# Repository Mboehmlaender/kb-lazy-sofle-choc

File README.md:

<div align="center">
  
<!-- Badges -->
<p>

</p>
   
<h4>
    <a href="https://github.com/Mboehmlaender/kb-lazy-sofle-choc">Documentation</a>
  <span> · </span>
    <a href="https://github.com/Mboehmlaender/kb-lazy-sofle-choc/issues/">Report Bug</a>
  <span> · </span>
    <a href="https://github.com/Mboehmlaender/kb-lazy-sofle-choc/issues/">Request Feature</a>
  </h4>
</div>

<br />
  <!--  -->
  <h1>LazySofleChoc</h1>
  
  <p>
The origianal Sofle is a 6×4+5 keys column-staggered split keyboard with encoder support. Based on [Lily58](https://github.com/kata0510/Lily58), [Corne](https://github.com/foostan/crkbd) and [Helix](https://github.com/MakotoKurauchi/helix) keyboards.

I removed three of the five thumb-cluster keys as i do not need them and i switched the firmware to VIAL. Those are the only varations that were made.

**[For more information and documentation visit https://josefadamcik.github.io/SofleKeyboard/](https://josefadamcik.github.io/SofleKeyboard/)**

SofleKeyboard was created by [Josef Adamcik](https://josef-adamcik.cz/). The motivation and process is covered in following blog-post: [Let me introduce you SofleKeyboard - a split keyboard based on Lily58 and Crkbd](https://josef-adamcik.cz/electronics/let-me-introduce-you-sofle-keyboard-split-keyboard-based-on-lily58.html). The Sofle Choc was designed by Brian Low and based on the excellent Sofle RGB by Dane Evans which was based on the original Sofle v2 by Josef Adamčík.

Sofle RGB was contributed by [Dane Evans](https://github.com/DaneEvans).

Sofle soldered was contributed by [kb-elmo](https://github.com/kb-elmo)

</p>

<!-- Table of Contents -->
# Table of Contents

- [About the Project](#about-the-project)
- [Features](#features)
- [Getting Started](#getting-started)
  * [List of materials](#list-of-materials)
  * [Necessary tools](#necessary-tools) 
  * [Optional tools](#optional-tools)
- [Build Guide](#build-guide)
- [Firmware](#firmware)
- [FAQ](#faq)
- [License](#license)
- [Acknowledgements](#acknowledgements)

<!-- About the Project -->
## About the Project
Description

<div align="center"> 
  
</div>

<!-- Features -->
### Features

- Feature 1
- Feature 2
- Feature 3

<!-- Getting Started -->
## Getting Started

<!-- List of Materials -->
### List of Materials

- 
- 
- 

<!-- Necessary tools -->
### Necessary tools
- 
-
-
   
<!-- Optional tools -->
### Optional tools
- 
-
-

<!-- Build Guide -->
### Build Guide

There is a detailled guide on how to build the Sofle Choc by Brian Lowe. Please refer to [this site](https://brianlow.notion.site/Sofle-Choc-Build-Guide-c4bbbaece6e746f7a5956842af567e79).

<!-- Firmware -->
## Firmware 

Sofle uses [Vial firmware](https://github.com/vial-kb/vial-qmk)

<!-- FAQ -->
## FAQ

- Question 1

  + Answer 1

- Question 2

  + Answer 2

<!-- License -->
## License

Licensed under MIT license

LazySofleChoc Project contains changes to the original product and / or the original product.
Sofle Choc under the MIT license.

Copyright (c) 2018 Josef Adamcik
https://github.com/josefadamcik/SofleKeyboard

SofleKeyboard Project contains changes to the original product and / or the original product.
Lily58 under the MIT license.

Copyright (c) 2018 Naoki Katahira
https://github.com/kata0510/Lily58

Lily58 Project contains changes to the original product and / or the original product.
Helix under the MIT license.

Copyright (c) 2018 MakotoKurauchi
https://github.com/MakotoKurauchi/helix

Lily58 Project contains changes to the original product and / or the original product.
crkbd under the MIT license.

Copyright (c) 2018 foostan
https://github.com/foostan/crkbd

Lily58 Project contains changes to the original product and / or the original product.
Ergo42 under the MIT license.

Copyright (c) 2017 Biacco42
https://github.com/Biacco42/Ergo42

<!-- Acknowledgments -->
## Acknowledgements

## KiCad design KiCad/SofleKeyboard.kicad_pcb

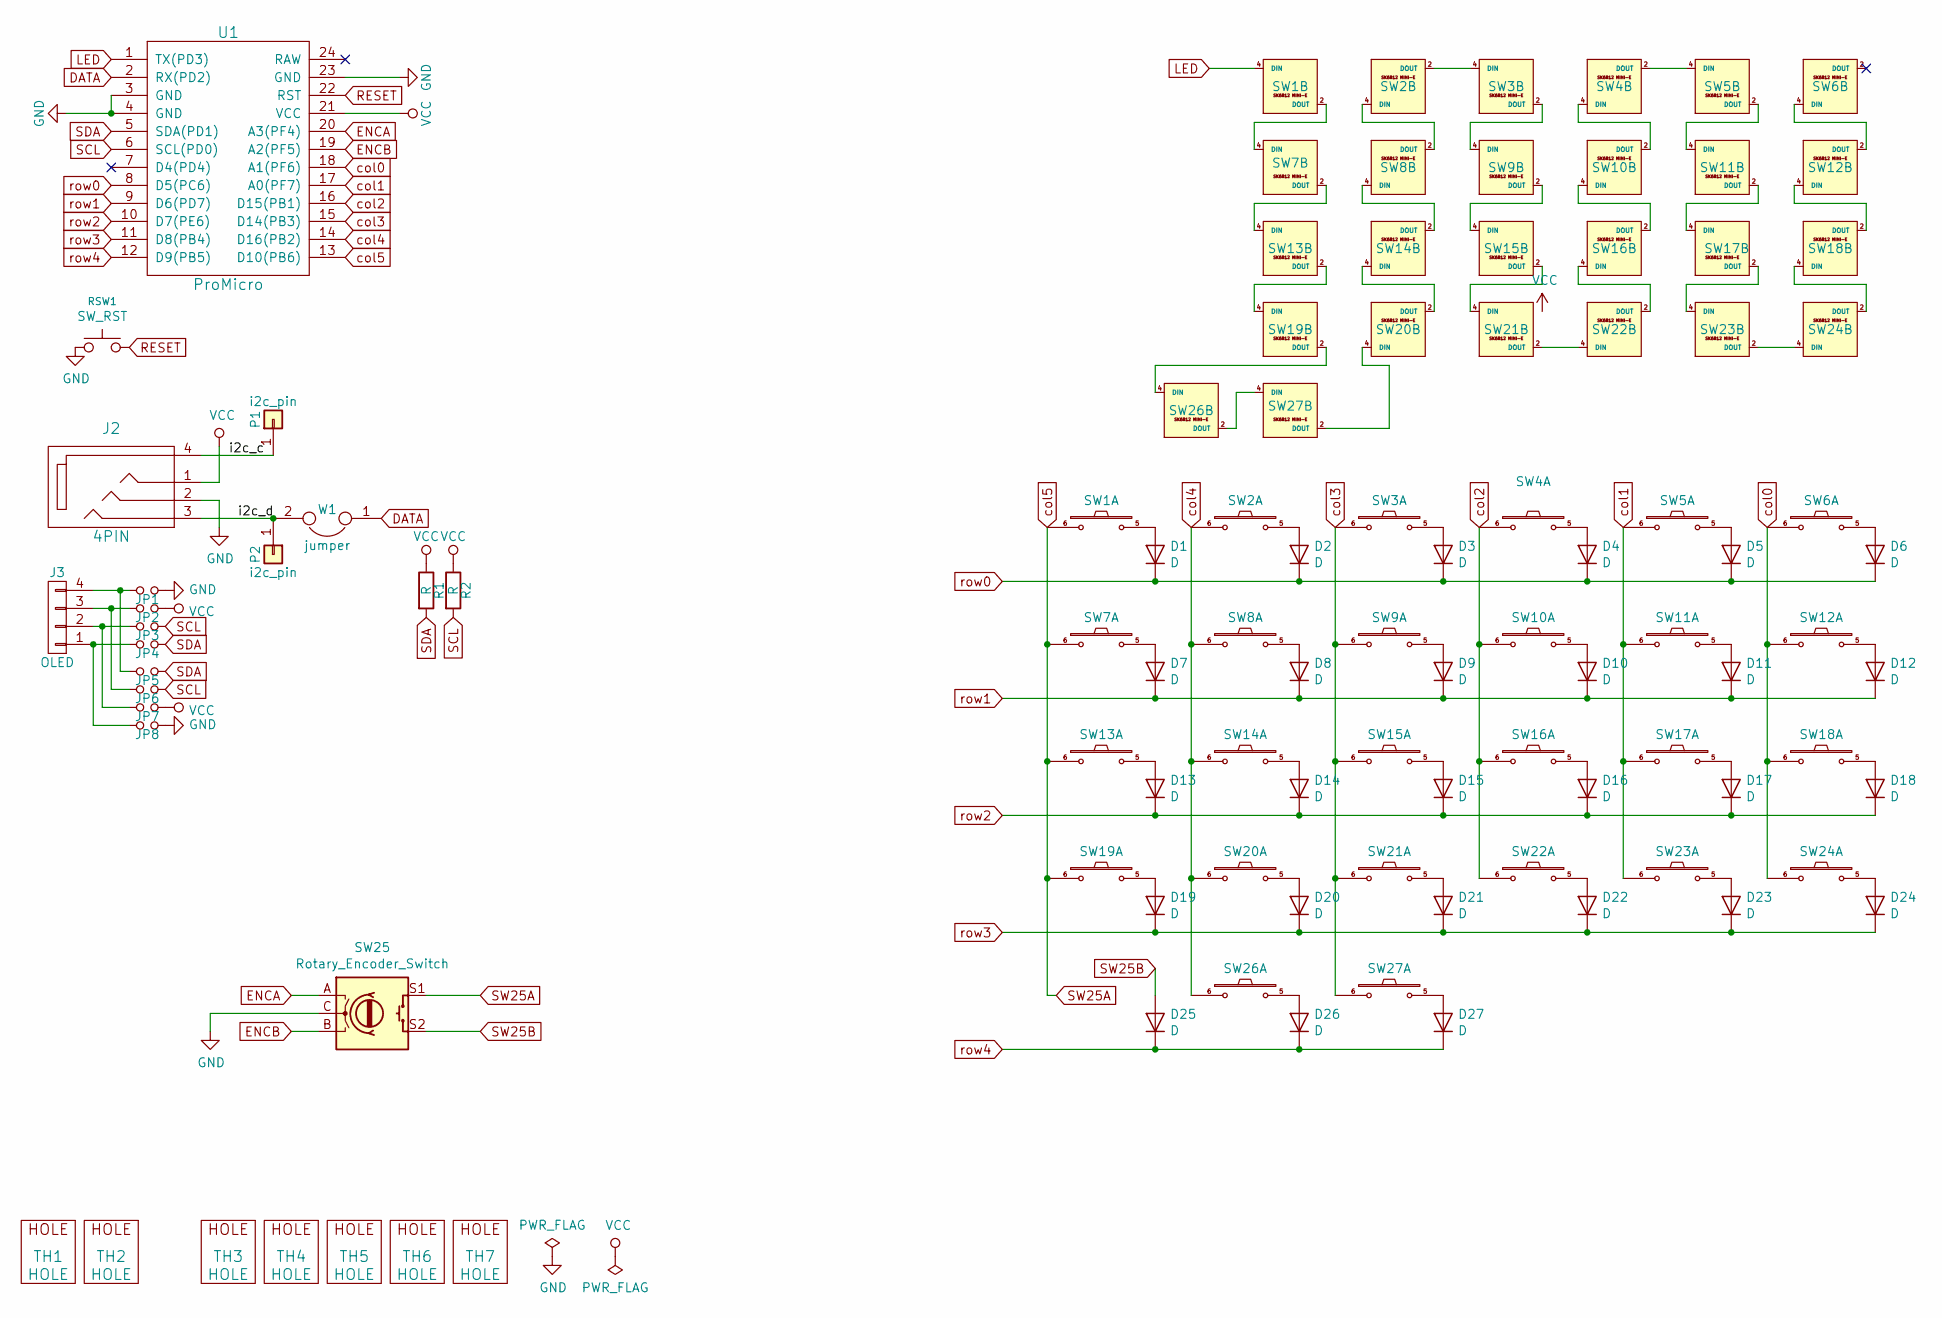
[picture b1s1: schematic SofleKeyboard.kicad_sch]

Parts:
D1, D2, D3, D4, D5, D6, D7, D8, D9, D10, D11, D12, D13, D14, D15, D16, D17, D18, D19, D20, D21, D22, D23, D24, D25, D26, D27: D; crkbd-diode
J2: 4PIN; MJ-4PP-9
J3: OLED; OLED_4Pin
JP1, JP2, JP3, JP4, JP5, JP6, JP7, JP8: Jumper_NO_Small; Jumper
P1, P2: i2c_pin; 1pin_conn
R1, R2: R; RESISTOR_mini
RSW1: SW_RST; TACT_SWITCH_TVBP06
SW1, SW2, SW3, SW4, SW5, SW6, SW7, SW8, SW9, SW10, SW11, SW12, SW13, SW14, SW15, SW16, SW17, SW18, SW19, SW20, SW21, SW22, SW23, SW24, SW26, SW27: SW_PUSH_LED; Choc_Hotswap_SK6812MiniE
SW25: Rotary_Encoder_Switch; RotaryEncoder_Alps_EC11E-Switch_Vertical_H20mm-keebio_modif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
TH1, TH2: HOLE; M2_HOLE_PCB
TH3, TH4, TH5, TH6, TH7: HOLE; HOLE_M2_TH
U1: ProMicro
W1: jumper; jumper_data

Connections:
/i2c_c: J2.4, P1.1
/i2c_d: J2.3, P2.1, W1.2
DATA: U1.2 (RX(PD2)), W1.1
ENCA: SW25.A, U1.20 (A3(PF4))
ENCB: SW25.B, U1.19 (A2(PF5))
GND: J2.2, JP1.2, JP8.2, RSW1.1, SW1.3 (GND), SW2.3 (GND), SW3.3 (GND), SW4.3 (GND), SW5.3 (GND), SW6.3 (GND), SW7.3 (GND), SW8.3 (GND), SW9.3 (GND), SW10.3 (GND), SW11.3 (GND), SW12.3 (GND), SW13.3 (GND), SW14.3 (GND), SW15.3 (GND), SW16.3 (GND), SW17.3 (GND), SW18.3 (GND), SW19.3 (GND), SW20.3 (GND), SW21.3 (GND), SW22.3 (GND), SW23.3 (GND), SW24.3 (GND), SW25.C, SW26.3 (GND), SW27.3 (GND), U1.3 (GND), U1.4 (GND), U1.23 (GND)
LED: SW1.4 (DIN), U1.1 (TX(PD3))
unnamed: D1.2 (A), SW1.5
unnamed: D2.2 (A), SW2.5
unnamed: D3.2 (A), SW3.5
unnamed: D4.2 (A), SW4.5
unnamed: D5.2 (A), SW5.5
unnamed: D6.2 (A), SW6.5
unnamed: D7.2 (A), SW7.5
unnamed: D8.2 (A), SW8.5
unnamed: D9.2 (A), SW9.5
unnamed: D10.2 (A), SW10.5
unnamed: D11.2 (A), SW11.5
unnamed: D12.2 (A), SW12.5
unnamed: D13.2 (A), SW13.5
unnamed: D14.2 (A), SW14.5
unnamed: D15.2 (A), SW15.5
unnamed: D16.2 (A), SW16.5
unnamed: D17.2 (A), SW17.5
unnamed: D18.2 (A), SW18.5
unnamed: D19.2 (A), SW19.5
unnamed: D20.2 (A), SW20.5
unnamed: D21.2 (A), SW21.5
unnamed: D22.2 (A), SW22.5
unnamed: D23.2 (A), SW23.5
unnamed: D24.2 (A), SW24.5
unnamed: D26.2 (A), SW26.5
unnamed: D27.2 (A), SW27.5
unnamed: J3.1, JP4.1, JP8.1
unnamed: J3.2, JP3.1, JP7.1
unnamed: J3.3, JP2.1, JP6.1
unnamed: J3.4, JP1.1, JP5.1
unnamed: SW1.2 (DOUT), SW7.4 (DIN)
unnamed: SW2.4 (DIN), SW8.2 (DOUT)
unnamed: SW2.2 (DOUT), SW3.4 (DIN)
unnamed: SW3.2 (DOUT), SW9.4 (DIN)
unnamed: SW4.2 (DOUT), SW5.4 (DIN)
unnamed: SW10.4 (DIN), SW16.2 (DOUT)
unnamed: SW4.4 (DIN), SW10.2 (DOUT)
unnamed: SW5.2 (DOUT), SW11.4 (DIN)
unnamed: SW11.2 (DOUT), SW17.4 (DIN)
unnamed: SW12.4 (DIN), SW18.2 (DOUT)
unnamed: SW6.4 (DIN), SW12.2 (DOUT)
unnamed: SW7.2 (DOUT), SW13.4 (DIN)
unnamed: SW13.2 (DOUT), SW19.4 (DIN)
unnamed: SW14.4 (DIN), SW20.2 (DOUT)
unnamed: SW8.4 (DIN), SW14.2 (DOUT)
unnamed: SW9.2 (DOUT), SW15.4 (DIN)
unnamed: SW15.2 (DOUT), SW21.4 (DIN)
unnamed: SW16.4 (DIN), SW22.2 (DOUT)
unnamed: SW17.2 (DOUT), SW23.4 (DIN)
unnamed: SW18.4 (DIN), SW24.2 (DOUT)
unnamed: SW19.2 (DOUT), SW26.4 (DIN)
unnamed: SW20.4 (DIN), SW27.2 (DOUT)
unnamed: SW21.2 (DOUT), SW22.4 (DIN)
unnamed: SW23.2 (DOUT), SW24.4 (DIN)
unnamed: SW26.2 (DOUT), SW27.4 (DIN)
RESET: RSW1.2, U1.22 (RST)
SCL: JP3.2, JP6.2, R2.2, U1.6 (SCL(PD0))
SDA: JP4.2, JP5.2, R1.2, U1.5 (SDA(PD1))
SW25A: SW1.6, SW7.6, SW13.6, SW19.6, SW25.S1, U1.13 (D10(PB6))
SW25B: D25.2 (A), SW25.S2
VCC: J2.1, JP2.2, JP7.2, R1.1, R2.1, SW1.1 (VDD), SW2.1 (VDD), SW3.1 (VDD), SW4.1 (VDD), SW5.1 (VDD), SW6.1 (VDD), SW7.1 (VDD), SW8.1 (VDD), SW9.1 (VDD), SW10.1 (VDD), SW11.1 (VDD), SW12.1 (VDD), SW13.1 (VDD), SW14.1 (VDD), SW15.1 (VDD), SW16.1 (VDD), SW17.1 (VDD), SW18.1 (VDD), SW19.1 (VDD), SW20.1 (VDD), SW21.1 (VDD), SW22.1 (VDD), SW23.1 (VDD), SW24.1 (VDD), SW26.1 (VDD), SW27.1 (VDD), U1.21 (VCC)
col0: SW6.6, SW12.6, SW18.6, SW24.6, U1.18 (A1(PF6))
col1: SW5.6, SW11.6, SW17.6, SW23.6, U1.17 (A0(PF7))
col2: SW4.6, SW10.6, SW16.6, SW22.6, U1.16 (D15(PB1))
col3: SW3.6, SW9.6, SW15.6, SW21.6, SW27.6, U1.15 (D14(PB3))
col4: SW2.6, SW8.6, SW14.6, SW20.6, SW26.6, U1.14 (D16(PB2))
row0: D1.1 (K), D2.1 (K), D3.1 (K), D4.1 (K), D5.1 (K), D6.1 (K), U1.8 (D5(PC6))
row1: D7.1 (K), D8.1 (K), D9.1 (K), D10.1 (K), D11.1 (K), D12.1 (K), U1.9 (D6(PD7))
row2: D13.1 (K), D14.1 (K), D15.1 (K), D16.1 (K), D17.1 (K), D18.1 (K), U1.10 (D7(PE6))
row3: D19.1 (K), D20.1 (K), D21.1 (K), D22.1 (K), D23.1 (K), D24.1 (K), U1.11 (D8(PB4))
row4: D25.1 (K), D26.1 (K), D27.1 (K), U1.12 (D9(PB5))

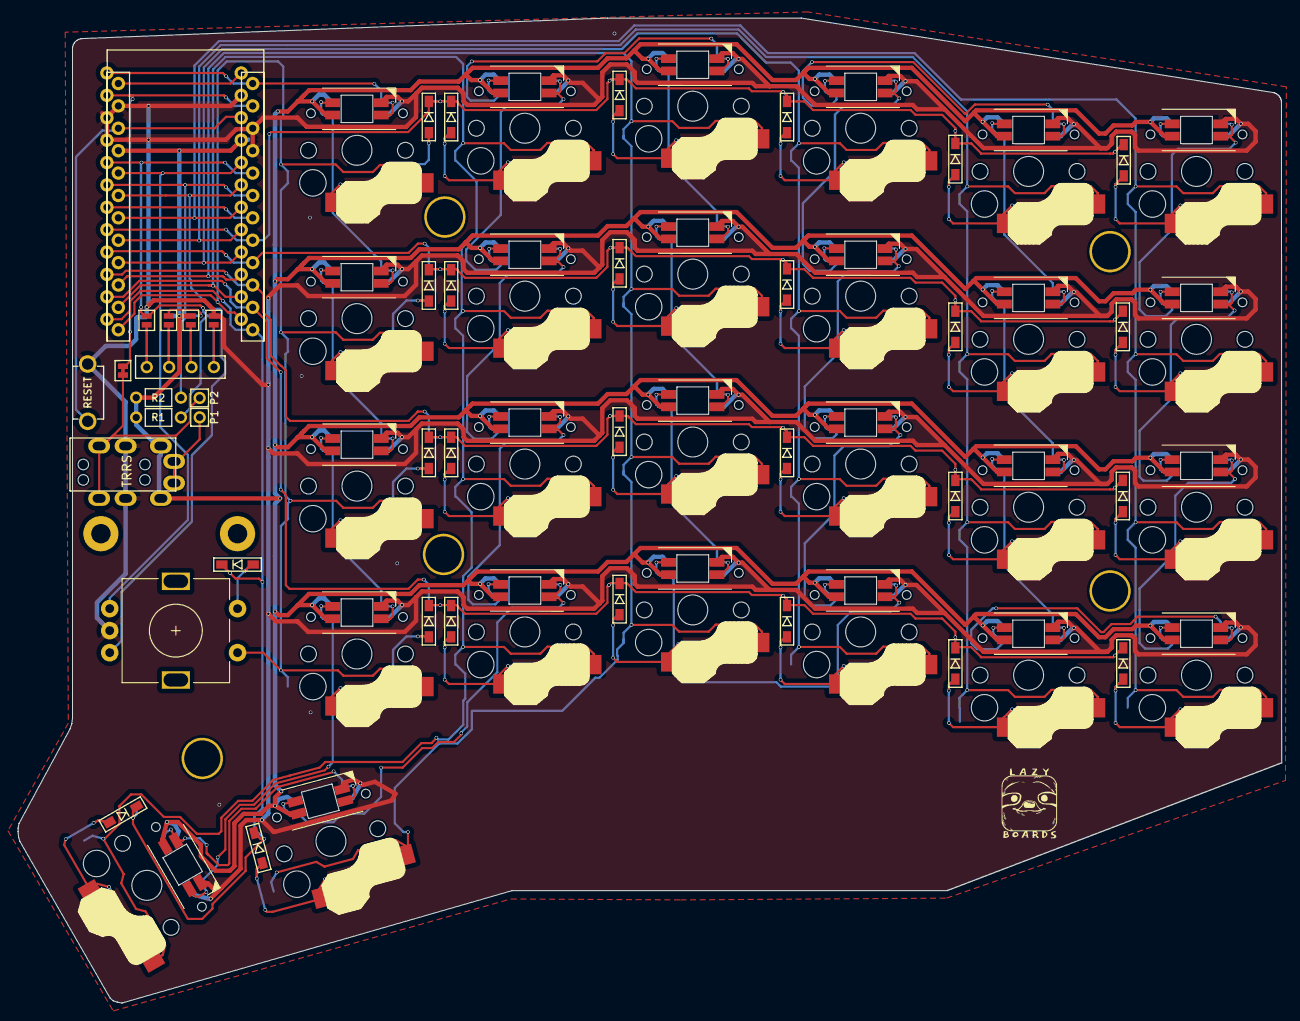
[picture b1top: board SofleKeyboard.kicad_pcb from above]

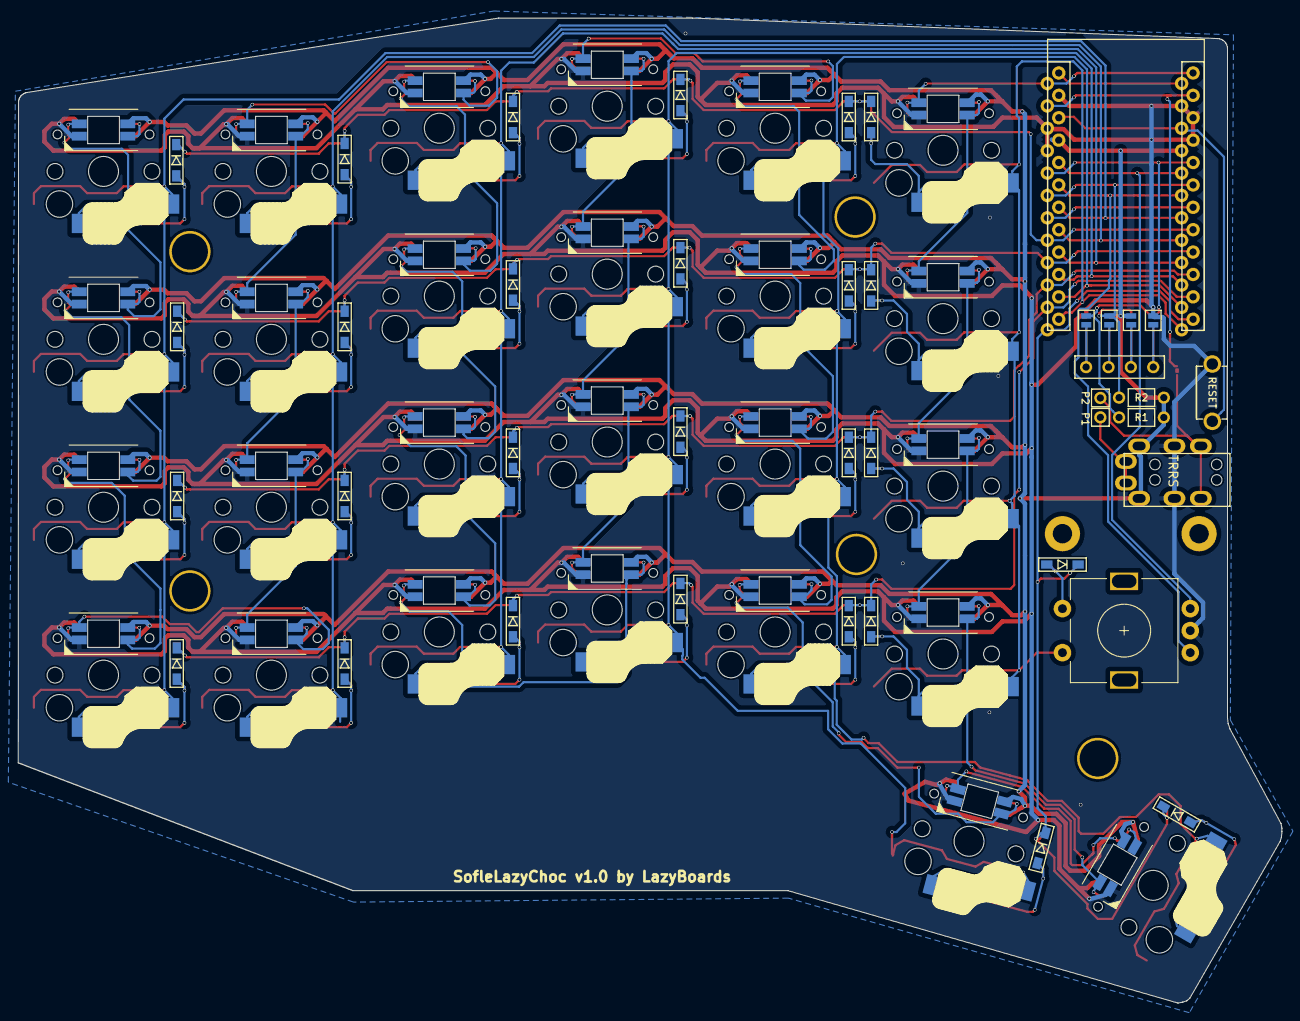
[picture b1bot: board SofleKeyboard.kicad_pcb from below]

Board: 2 copper layers, 143.4 x 111.8 mm, 78 parts (4 on the bottom side), 78 nets.

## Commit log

2024-02-26 Update LICENSE
2024-02-26 Create Bla
2024-12-03 Backups
2025-01-01 gitignore
2025-01-02 Add original Firmware
